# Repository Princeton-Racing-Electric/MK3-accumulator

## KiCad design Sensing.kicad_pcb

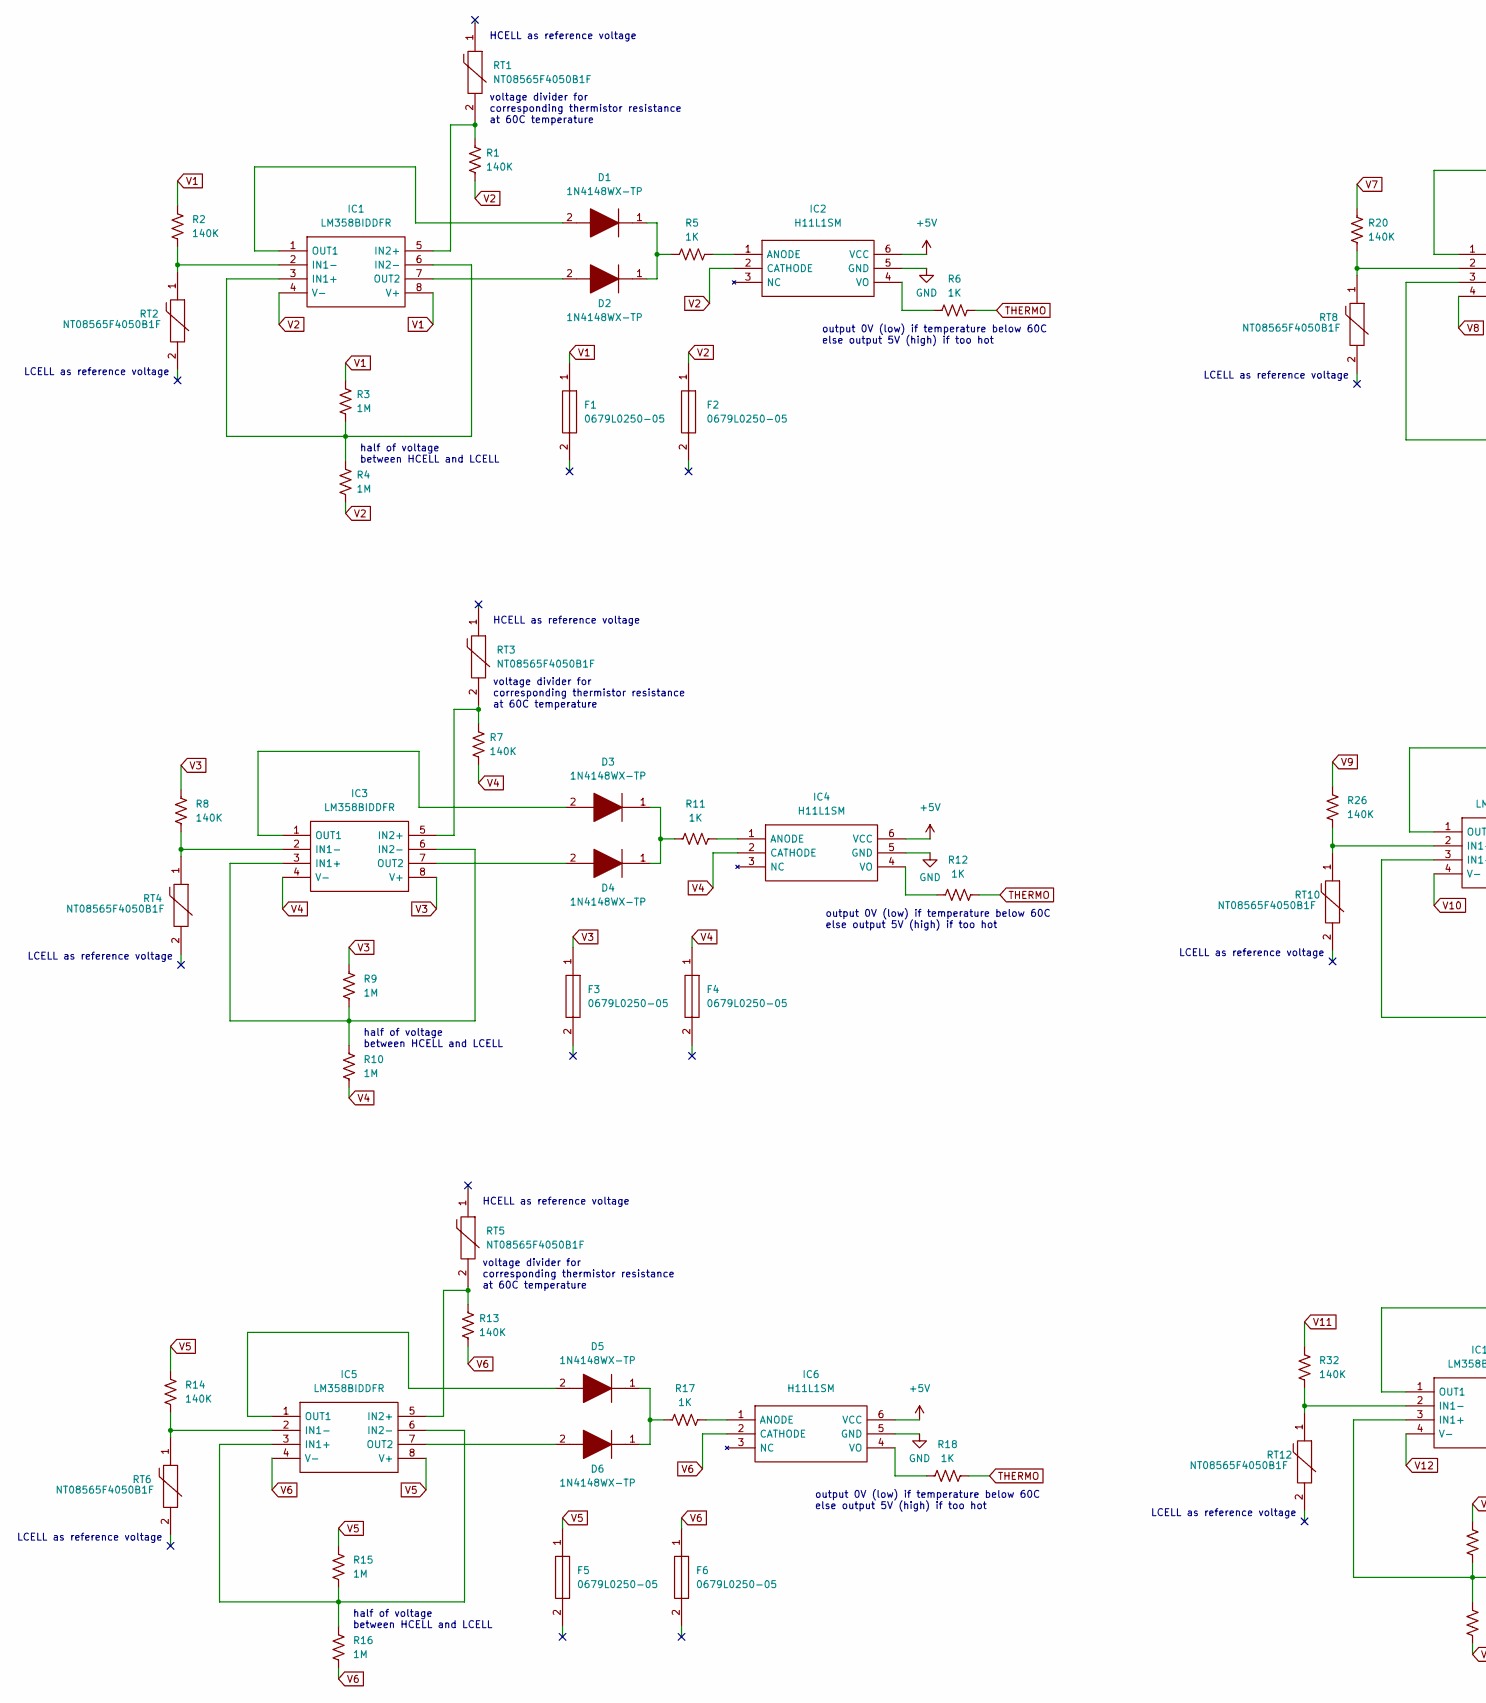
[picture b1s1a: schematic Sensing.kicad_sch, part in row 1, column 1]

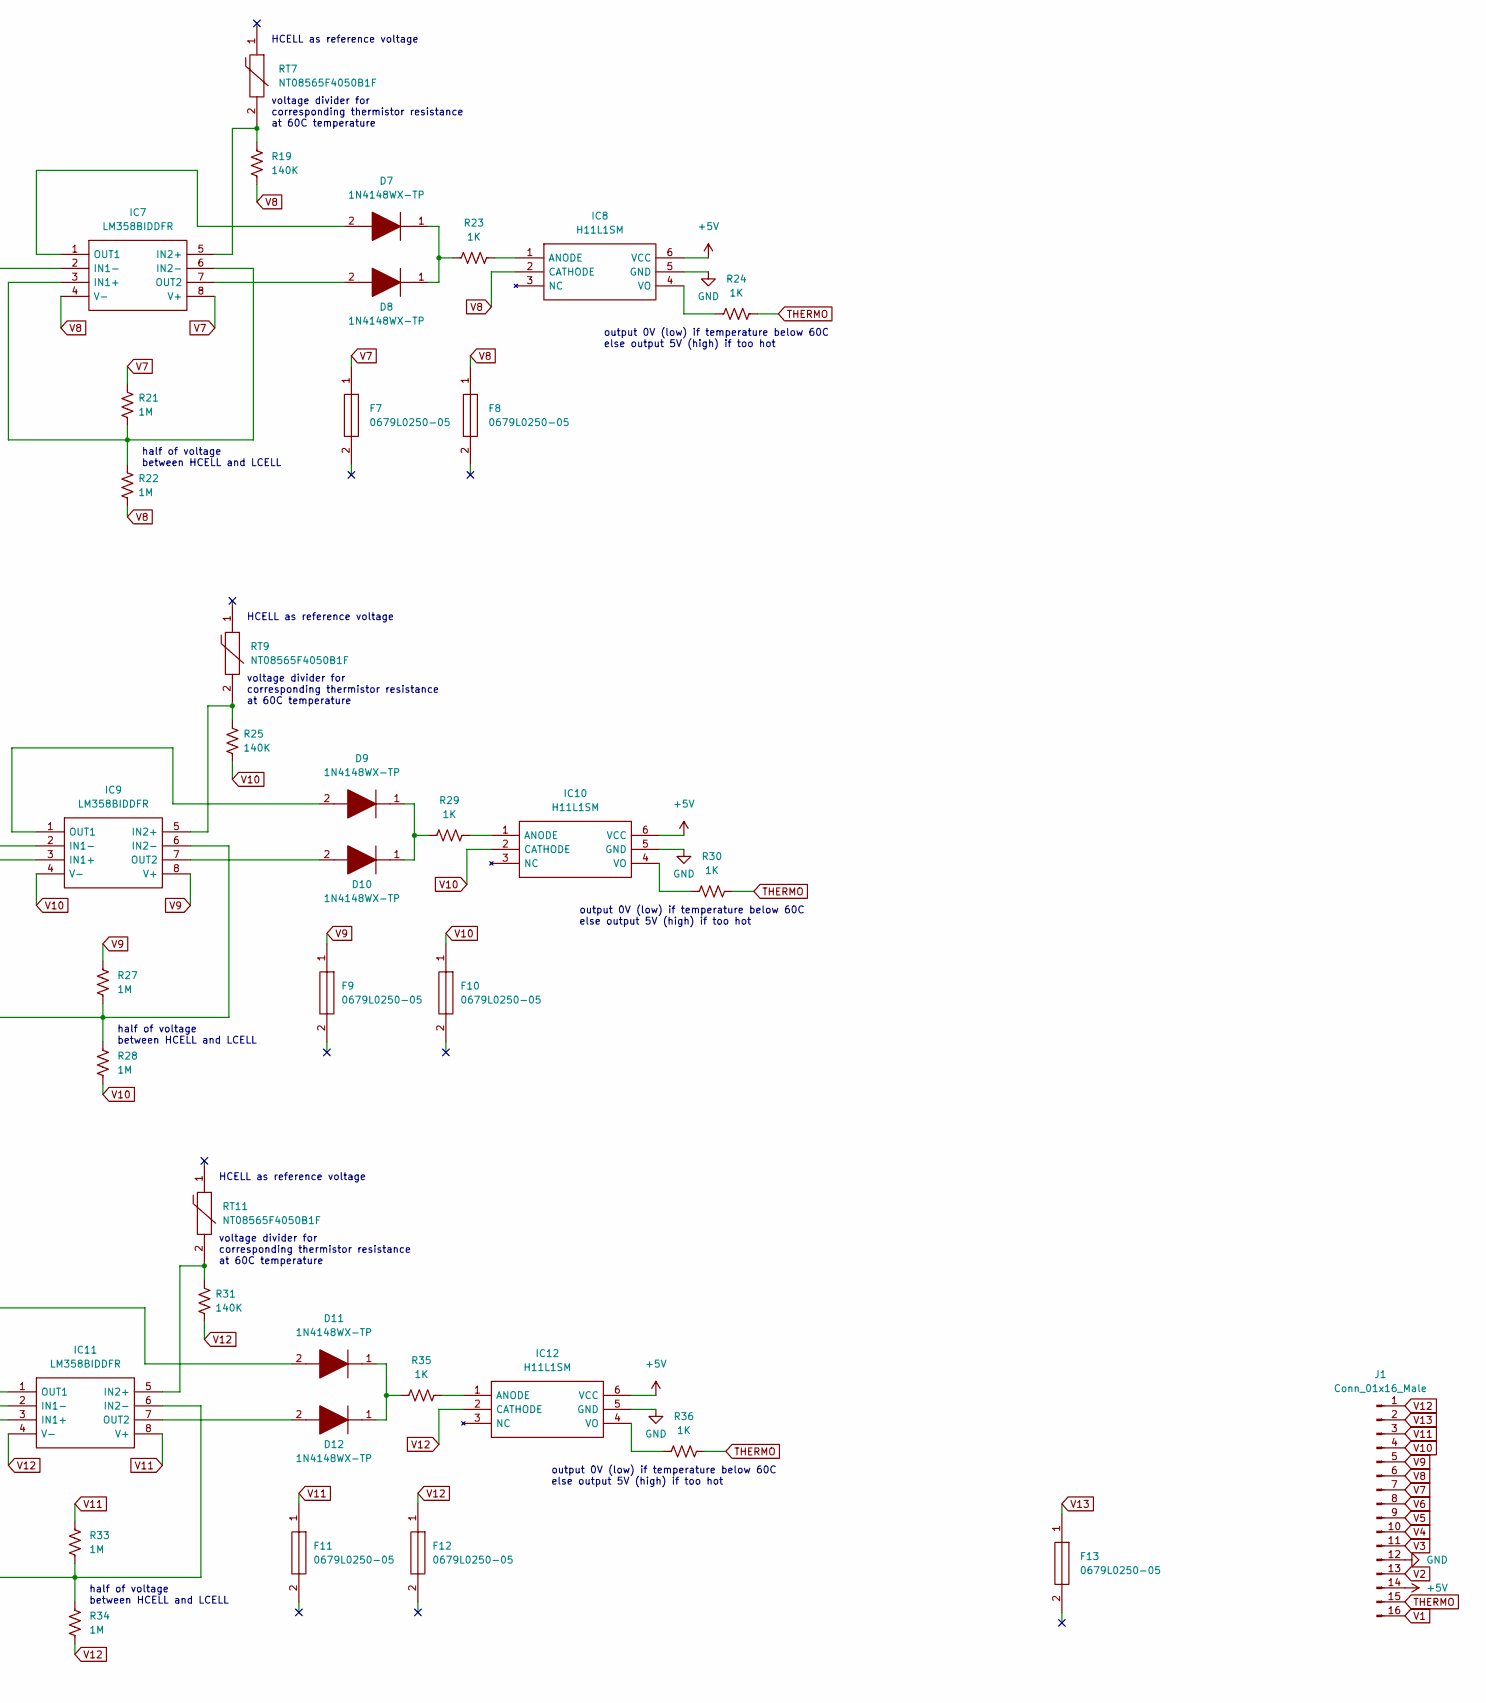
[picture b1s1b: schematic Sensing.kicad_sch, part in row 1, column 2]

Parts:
D1, D2, D3, D4, D5, D6, D7, D8, D9, D10, D11, D12: 1N4148WX-TP; SOD2512X115N; Mouser Part Number 833-1N4148WX-TP
F1, F2, F3, F4, F5, F6, F7, F8, F9, F10, F11, F12, F13: 0679L0250-05; FUSC6125X279N; Mouser Part Number 530-0679L0250-05
IC1, IC3, IC5, IC7, IC9, IC11: LM358BIDDFR; SOT65P280X110-8N; Mouser Part Number 595-LM358BIDDFR
IC2, IC4, IC6, IC8, IC10, IC12: H11L1SM; SMT-6PIN-_LEAD-BEND_; Mouser Part Number 512-H11L1SM
J1: Conn_01x16_Male; Hirose_DF11-16DP-2DSA_2x08_P2.00mm_Vertical
R1, R2, R7, R8, R13, R14, R19, R20, R25, R26, R31, R32: 140K; R_0805_2012Metric_Pad1.20x1.40mm_HandSolder
R3, R4, R9, R10, R15, R16, R21, R22, R27, R28, R33, R34: 1M; R_0805_2012Metric_Pad1.20x1.40mm_HandSolder
R5, R6, R11, R12, R17, R18, R23, R24, R29, R30, R35, R36: 1K; R_0805_2012Metric_Pad1.20x1.40mm_HandSolder
RT1, RT2, RT3, RT4, RT5, RT6, RT7, RT8, RT9, RT10, RT11, RT12: NT08565F4050B1F; THRMC2012X90N; Manufacturer_Part_Number NT08565F4050B1F

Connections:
+5V: IC2.6 (VCC), IC4.6 (VCC), IC6.6 (VCC), IC8.6 (VCC), IC10.6 (VCC), IC12.6 (VCC), J1.14
GND: IC2.5 (GND), IC4.5 (GND), IC6.5 (GND), IC8.5 (GND), IC10.5 (GND), IC12.5 (GND), J1.12
unnamed: D1.1, D2.1, R5.1
unnamed: D1.2, IC1.1 (OUT1)
unnamed: D2.2, IC1.7 (OUT2)
unnamed: D3.1, D4.1, R11.1
unnamed: D3.2, IC3.1 (OUT1)
unnamed: D4.2, IC3.7 (OUT2)
unnamed: D5.1, D6.1, R17.1
unnamed: D5.2, IC5.1 (OUT1)
unnamed: D6.2, IC5.7 (OUT2)
unnamed: D7.1, D8.1, R23.1
unnamed: D7.2, IC7.1 (OUT1)
unnamed: D8.2, IC7.7 (OUT2)
unnamed: D9.2, IC9.1 (OUT1)
unnamed: D9.1, D10.1, R29.1
unnamed: D10.2, IC9.7 (OUT2)
unnamed: D11.1, D12.1, R35.1
unnamed: D11.2, IC11.1 (OUT1)
unnamed: D12.2, IC11.7 (OUT2)
unnamed: IC1.2 (IN1-), R2.2, RT2.1
unnamed: IC1.3 (IN1+), IC1.6 (IN2-), R3.2, R4.1
unnamed: IC1.5 (IN2+), R1.1, RT1.2
unnamed: IC2.1 (ANODE), R5.2
unnamed: IC2.4 (VO), R6.2
unnamed: IC3.2 (IN1-), R8.2, RT4.1
unnamed: IC3.3 (IN1+), IC3.6 (IN2-), R9.2, R10.1
unnamed: IC3.5 (IN2+), R7.1, RT3.2
unnamed: IC4.1 (ANODE), R11.2
unnamed: IC4.4 (VO), R12.2
unnamed: IC5.2 (IN1-), R14.2, RT6.1
unnamed: IC5.3 (IN1+), IC5.6 (IN2-), R15.2, R16.1
unnamed: IC5.5 (IN2+), R13.1, RT5.2
unnamed: IC6.1 (ANODE), R17.2
unnamed: IC6.4 (VO), R18.2
unnamed: IC7.2 (IN1-), R20.2, RT8.1
unnamed: IC7.3 (IN1+), IC7.6 (IN2-), R21.2, R22.1
unnamed: IC7.5 (IN2+), R19.1, RT7.2
unnamed: IC8.1 (ANODE), R23.2
unnamed: IC8.4 (VO), R24.2
unnamed: IC9.2 (IN1-), R26.2, RT10.1
unnamed: IC9.3 (IN1+), IC9.6 (IN2-), R27.2, R28.1
unnamed: IC9.5 (IN2+), R25.1, RT9.2
unnamed: IC10.1 (ANODE), R29.2
unnamed: IC10.4 (VO), R30.2
unnamed: IC11.2 (IN1-), R32.2, RT12.1
unnamed: IC11.3 (IN1+), IC11.6 (IN2-), R33.2, R34.1
unnamed: IC11.5 (IN2+), R31.1, RT11.2
unnamed: IC12.1 (ANODE), R35.2
unnamed: IC12.4 (VO), R36.2
THERMO: J1.15, R6.1, R12.1, R18.1, R24.1, R30.1, R36.1
V1: F1.1, IC1.8 (V+), J1.16, R2.1, R3.1
V2: F2.1, IC1.4 (V-), IC2.2 (CATHODE), J1.13, R1.2, R4.2
V3: F3.1, IC3.8 (V+), J1.11, R8.1, R9.1
V4: F4.1, IC3.4 (V-), IC4.2 (CATHODE), J1.10, R7.2, R10.2
V5: F5.1, IC5.8 (V+), J1.9, R14.1, R15.1
V6: F6.1, IC5.4 (V-), IC6.2 (CATHODE), J1.8, R13.2, R16.2
V7: F7.1, IC7.8 (V+), J1.7, R20.1, R21.1
V8: F8.1, IC7.4 (V-), IC8.2 (CATHODE), J1.6, R19.2, R22.2
V9: F9.1, IC9.8 (V+), J1.5, R26.1, R27.1
V10: F10.1, IC9.4 (V-), IC10.2 (CATHODE), J1.4, R25.2, R28.2
V11: F11.1, IC11.8 (V+), J1.3, R32.1, R33.1
V12: F12.1, IC11.4 (V-), IC12.2 (CATHODE), J1.1, R31.2, R34.2
V13: F13.1, J1.2

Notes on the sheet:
output 0V (low) if temperature below 60C else output 5V (high) if too hot
HCELL as reference voltage
voltage divider for corresponding thermistor resistance at 60C temperature
LCELL as reference voltage
half of voltage between HCELL and LCELL

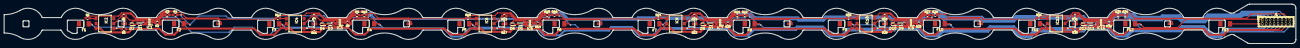
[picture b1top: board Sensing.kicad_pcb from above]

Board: 2 copper layers, 655.9 x 20.0 mm, 86 parts (0 on the bottom side), 64 nets.

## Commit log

2023-04-15 first pass at forward positive board
2023-04-15 added shorter connector
2023-04-15 organizing
2023-04-15 small edits
